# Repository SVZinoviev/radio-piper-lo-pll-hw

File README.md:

# 100 - 200 MHz PLL

## Intended use

Radio LO1 and LO2 configurable synthesizer.

## Configuration

VCO can work in the wide range 10 MHz - 200+ MHz

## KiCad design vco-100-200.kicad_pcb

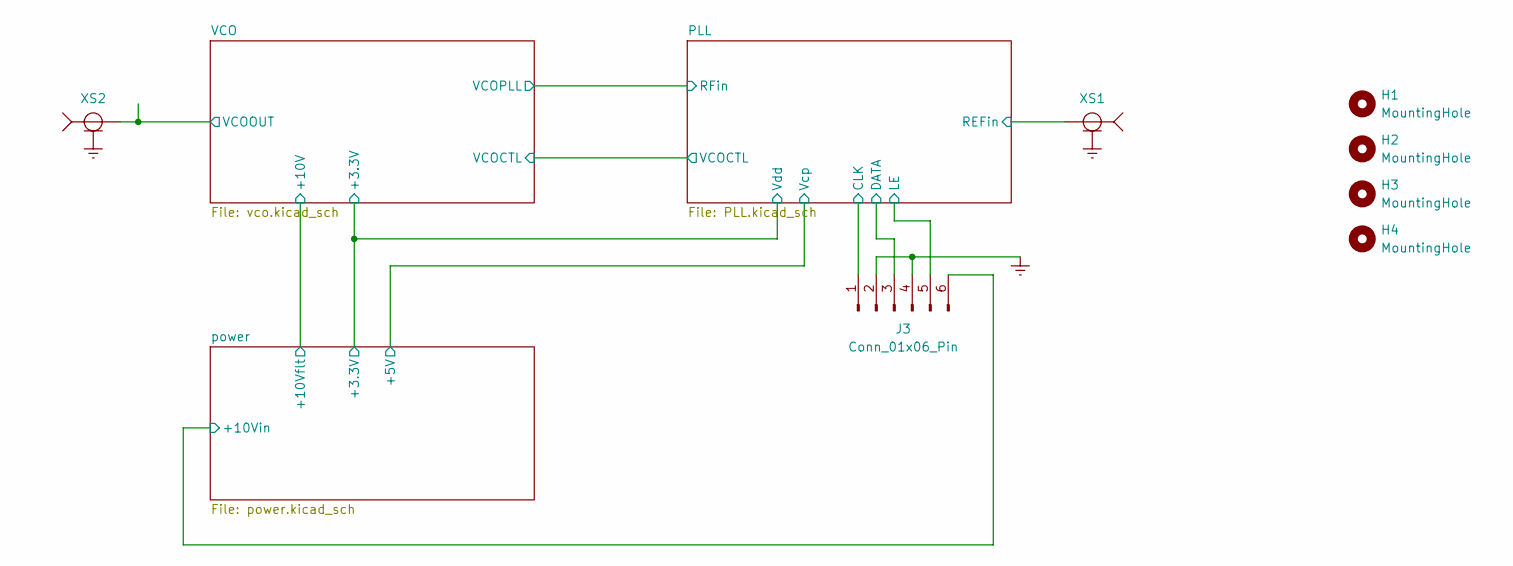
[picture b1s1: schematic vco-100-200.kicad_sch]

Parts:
H1, H2, H3, H4: MountingHole; MountingHole_3.2mm_M3
J3: Conn_01x06_Pin; PinHeader_1x06_P2.54mm_Vertical
XS1, XS2: RF-PCB-pin-place

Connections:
/PLL/CLK: J3.1; also elsewhere on the board
/PLL/DATA: J3.3; also elsewhere on the board
/PLL/LE: J3.5; also elsewhere on the board
/PLL/REFin: XS1.1; also elsewhere on the board
/VCO/VCOOUT: XS2.1; also elsewhere on the board
/power/+10Vin: J3.6; also elsewhere on the board
Earth: J3.2, J3.4, XS1.2, XS2.2; also elsewhere on the board

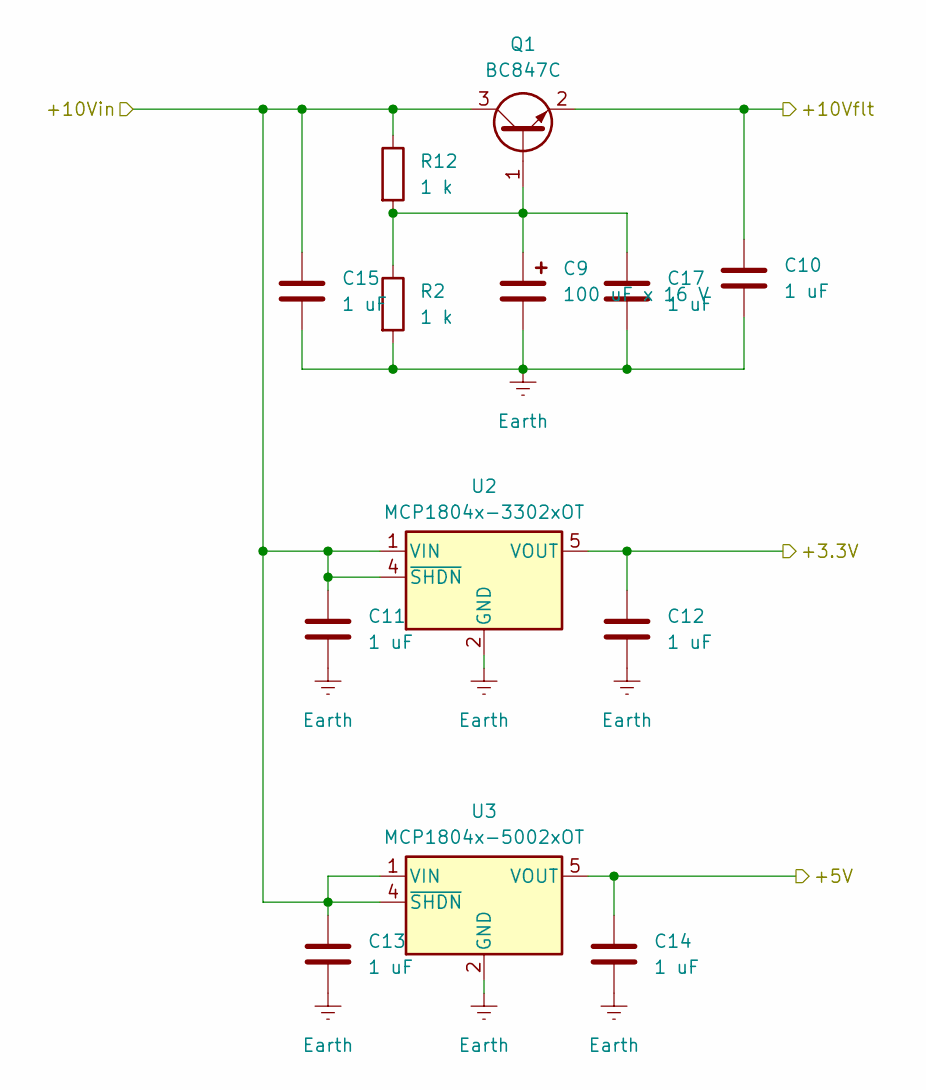
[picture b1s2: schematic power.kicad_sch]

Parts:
C9: 100 uF x 16 V; CP_Elec_6.3x5.8; Partnumber UCD1C101MCL1GS
C10, C11, C12, C13, C14, C15, C17: 1 uF; C_0603_1608Metric; Partnumber GCM188R71C105KA64D
Q1: BC847C; SOT-23; Partnumber BC847C
R2, R12: 1 k; R_0603_1608Metric; Partnumber RC0603JR-071K00L
U2: MCP1804x-3302xOT; SOT-23-5
U3: MCP1804x-5002xOT; SOT-23-5

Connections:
/PLL/Vcp: C14.1, U3.5 (VOUT); also elsewhere on the board
/PLL/Vdd: C12.1, U2.5 (VOUT); also elsewhere on the board
/VCO/+10V: C10.1, Q1.2 (E); also elsewhere on the board
/power/+10Vin: C11.1, C13.1, C15.1, Q1.3 (C), R12.1, U2.1 (VIN), U2.4 (~SHDN), U3.1 (VIN), U3.4 (~SHDN); also elsewhere on the board
Earth: C9.2, C10.2, C11.2, C12.2, C13.2, C14.2, C15.2, C17.2, R2.2, U2.2 (GND), U3.2 (GND); also elsewhere on the board
unnamed: C9.1, C17.1, Q1.1 (B), R2.1, R12.2

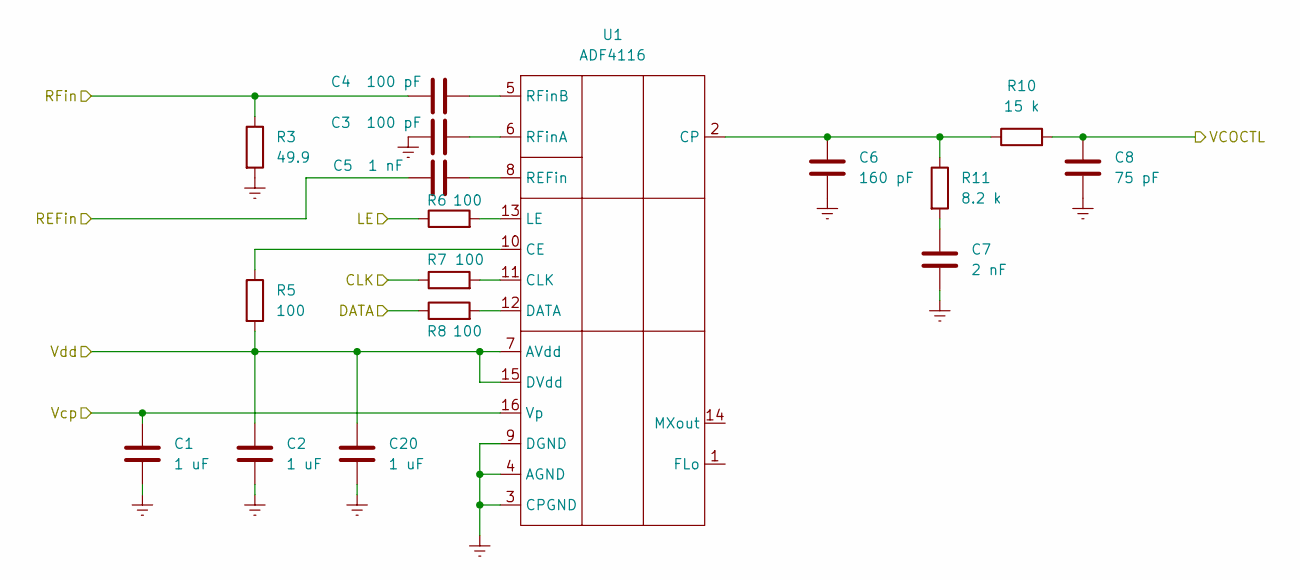
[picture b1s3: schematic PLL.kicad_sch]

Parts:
C1, C2, C20: 1 uF; C_0603_1608Metric; Partnumber GCM188R71C105KA64D
C3, C4: 100 pF; C_0603_1608Metric; Partnumber CC0603JRNPO9BN101
C5: 1 nF; C_0603_1608Metric; Partnumber CC0603JRNPO9BN102
C6: 160 pF; C_0603_1608Metric; Partnumber GCM1885C2A161GA16J
C7: 2 nF; C_0603_1608Metric; Partnumber GRM1885C1H222JA01D
C8: 75 pF; C_0603_1608Metric; Partnumber GCM1885C2A750JA16D
R3: 49.9; R_0603_1608Metric; Partnumber RC0603FR-0749R9L
R5, R6, R7, R8: 100; R_0603_1608Metric; Partnumber RC0603JR-07100RL
R10: 15 k; R_0603_1608Metric; Partnumber RC0603JR-0715K0L
R11: 8.2 k; R_0603_1608Metric; Partnumber RC0603FR-078K2L
U1: ADF4116; TSSOP-16_4.4x5mm_P0.65mm; Partnumber ADF4116BRUZ

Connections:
/PLL/CLK: R7.1; also elsewhere on the board
/PLL/DATA: R8.1; also elsewhere on the board
/PLL/LE: R6.1; also elsewhere on the board
/PLL/REFin: C5.2; also elsewhere on the board
/PLL/RFin: C4.1, R3.1; also elsewhere on the board
/PLL/VCOCTL: C8.1, R10.2; also elsewhere on the board
/PLL/Vcp: C1.1, U1.16 (Vp); also elsewhere on the board
/PLL/Vdd: C2.1, C20.1, R5.2, U1.7 (AVdd), U1.15 (DVdd); also elsewhere on the board
Earth: C1.2, C2.2, C3.1, C6.2, C7.2, C8.2, C20.2, R3.2, U1.3 (CPGND), U1.4 (AGND), U1.9 (DGND); also elsewhere on the board
unnamed: C7.1, R11.2
unnamed: R5.1, U1.10 (CE)
unnamed: R7.2, U1.11 (CLK)
unnamed: C6.1, R10.1, R11.1, U1.2 (CP)
unnamed: R8.2, U1.12 (DATA)
unnamed: R6.2, U1.13 (LE)
unnamed: C5.1, U1.8 (REFin)
unnamed: C3.2, U1.6 (RFinA)
unnamed: C4.2, U1.5 (RFinB)

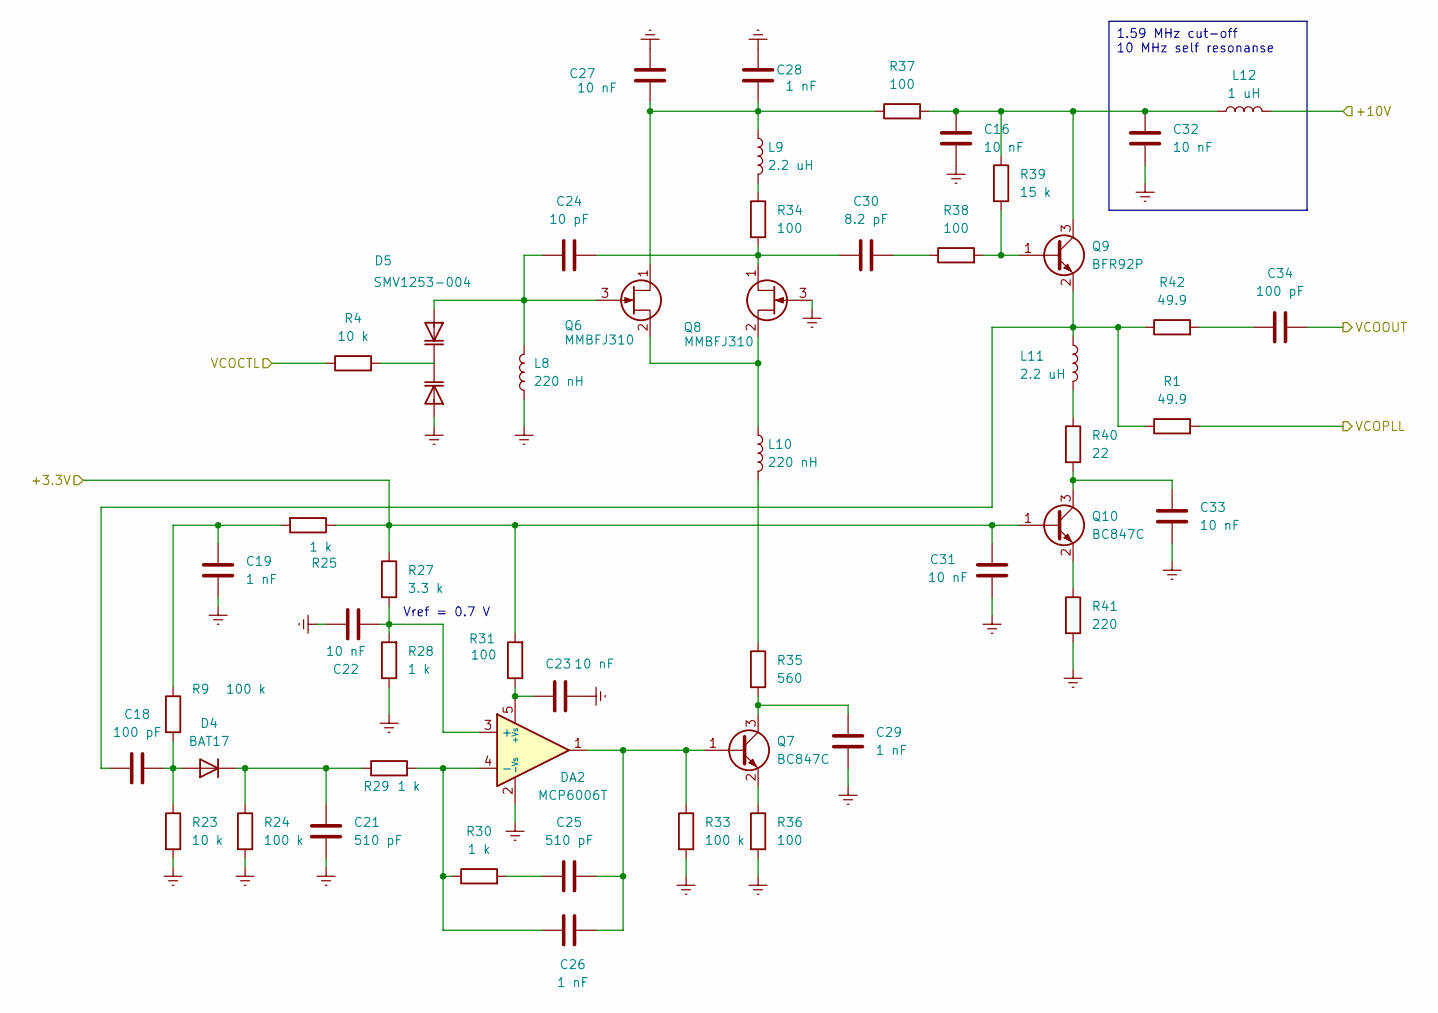
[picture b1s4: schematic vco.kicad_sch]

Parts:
C16, C22, C23, C27, C31, C32, C33: 10 nF; C_0603_1608Metric; Partnumber CC0603JRNPO9BN103
C18, C34: 100 pF; C_0603_1608Metric; Partnumber CC0603JRNPO9BN101
C19, C26, C28, C29: 1 nF; C_0603_1608Metric; Partnumber CC0603JRNPO9BN102
C21, C25: 510 pF; C_0603_1608Metric; Partnumber CC0603JRNPO9BN511
C24: 10 pF; C_0603_1608Metric; Partnumber CC0603JRNPO9BN100
C30: 8.2 pF; C_0603_1608Metric; Partnumber CC0603JRNPO9BN8R2
D4: BAT17; SOT-23; Partnumber BAT17E6327HTSA1
D5: SMV1253-004; SOT-23; Partnumber SMV1253-004LF
DA2: MCP6006T; SOT-23-5
L8, L10: 220 nH; L_1008_2520Metric; Partnumber LQW2BASR22J00L
L9, L11: 2.2 uH; L_1008_2520Metric; Partnumber LQW2UAS2R2J00L
L12: 1 uH; L_0603_1608Metric; Partnumber MLZ1608A1R0WT000
Q6, Q8: MMBFJ310; SOT-23; Partnumber MMBFJ310
Q7, Q10: BC847C; SOT-23; Partnumber BC847C
Q9: BFR92P; SOT-23; Partnumber BFR92PE6327HTSA1
R1, R42: 49.9; R_0603_1608Metric; Partnumber RC0603FR-0749R9L
R4, R23: 10 k; R_0603_1608Metric; Partnumber RC0603JR-0710K0L
R9, R24, R33: 100 k; R_0603_1608Metric; Partnumber RC0603JR-07100KL
R25, R28, R29, R30: 1 k; R_0603_1608Metric; Partnumber RC0603JR-071K00L
R27: 3.3 k; R_0603_1608Metric; Partnumber RC0603JR-073K30L
R31, R34, R36, R37, R38: 100; R_0603_1608Metric; Partnumber RC0603JR-07100RL
R35: 560; R_0603_1608Metric; Partnumber RC0603JR-07560RL
R39: 15 k; R_0603_1608Metric; Partnumber RC0603JR-0715K0L
R40: 22; R_0603_1608Metric; Partnumber RC0603JR-0722RL
R41: 220; R_0603_1608Metric; Partnumber RC0603JR-07220RL

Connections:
/PLL/RFin: R1.2; also elsewhere on the board
/PLL/VCOCTL: R4.1; also elsewhere on the board
/PLL/Vdd: C31.2, Q10.1 (B), R25.1, R27.1, R31.2; also elsewhere on the board
/VCO/+10V: L12.2; also elsewhere on the board
/VCO/VCOOUT: C34.2; also elsewhere on the board
Earth: C16.2, C19.2, C21.1, C22.1, C23.2, C27.2, C28.2, C29.2, C31.1, C32.2, C33.2, D5.2 (A2), DA2.2 (-Vs), L8.1, Q8.3 (G), R23.2, R24.2, R28.1, R33.2, R36.2, R41.2; also elsewhere on the board
unnamed: C19.1, R9.1, R25.2
unnamed: C25.1, R30.2
unnamed: C30.2, R38.1
unnamed: C34.1, R42.2
unnamed: C18.2, D4.1 (A), R9.2, R23.1
unnamed: C21.2, D4.3 (K), R24.1, R29.1
unnamed: C24.1, D5.1 (A1), L8.2, Q6.3 (G)
unnamed: D5.3 (K), R4.2
unnamed: C22.2, DA2.3 (+), R27.2, R28.2
unnamed: C23.1, DA2.5 (+Vs), R31.1
unnamed: C26.1, DA2.4 (-), R29.2, R30.1
unnamed: L9.2, R34.1
unnamed: L10.2, R35.1
unnamed: L11.2, R40.1
unnamed: C27.1, C28.1, L9.1, Q6.1 (D), R37.1
unnamed: L10.1, Q6.2 (S), Q8.2 (S)
unnamed: C25.2, C26.2, DA2.1, Q7.1 (B), R33.1
unnamed: C29.1, Q7.3 (C), R35.2
unnamed: Q7.2 (E), R36.1
unnamed: C24.2, C30.1, Q8.1 (D), R34.2
unnamed: Q9.1 (B), R38.2, R39.2
unnamed: C16.1, C32.1, L12.1, Q9.3 (C), R37.2, R39.1
unnamed: C18.1, L11.1, Q9.2 (E), R1.1, R42.1
unnamed: C33.1, Q10.3 (C), R40.2
unnamed: Q10.2 (E), R41.1

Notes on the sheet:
Vref = 0.7 V
1.59 MHz cut-off 10 MHz self resonanse

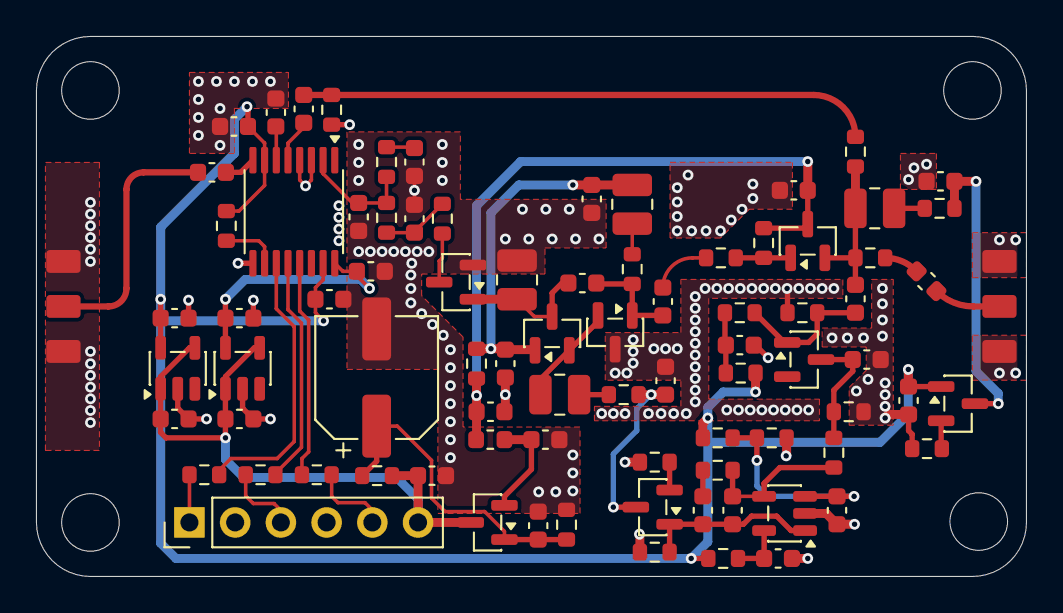
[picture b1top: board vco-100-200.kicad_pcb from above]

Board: 4 copper layers, 55.0 x 30.0 mm, 88 parts (0 on the bottom side), 47 nets.

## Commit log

2026-02-12 Add project files to the repo. Initial version
2026-02-13 Update pcb routing, add 50 Ohm net classes
